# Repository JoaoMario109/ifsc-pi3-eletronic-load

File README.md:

<div id="top"></div>

<!-- PROJECT LOGO -->
<br />
<div align="center">

  <h3 align="center">Simple Electronic Load</h3>

  <p align="center">
    <br />
    <br />
    <a href="https://github.com/JoaoMario109/ifsc-pi3-eletronic-load/issues">Report Bug</a>
    ·
    <a href="https://github.com/JoaoMario109/ifsc-pi3-eletronic-load/issues">Request Feature</a>
  </p>
</div>

<!-- TABLE OF CONTENTS -->
<details>
  <summary>Table of Contents</summary>
  <ol>
    <li>
      <a href="#about-the-project">About The Project</a>
      <ul>
        <li><a href="#about-the-project-overview">Overview</a></li>
      </ul>
    </li>
    <li>
      <a href="#license">License</a>
    </li>
    <li>
      <a href="#contact">Contacts</a>
    </li>
  </ol>
</details>

<!-- ABOUT THE PROJECT -->
<div id="about-the-project"></div>

## About The Project

This project is the implementation of a simple electronic load with WiFi integration and the ability to operate using custom waveforms. It forms part of (PI3) for the Electronics Engineering course at IFSC, Campus Florianópolis.

<div id="about-the-project-overview"></div>

### Overview

The electronic load is designed to handle up to 100W of power and supports four different operating modes: constant current, constant power, constant resistance, and constant voltage. Additionally, it can execute custom waveforms uploaded via its various communication interfaces.

The load is divided into three key modules:
1. **Power Module** – Contains the hardware components responsible for handling the load, such as the power transistors and other essential elements.
2. **Control Module** – Manages the desired operating mode and ensures the system maintains the appropriate levels of current, voltage, or resistance.
3. **Communication Module** – Facilitates interaction between the user and the device via WiFi, USB, or other interfaces, and stores custom waveforms on an SD card for future use.

The device can be accessed through its control panel, WiFi, or USB interface, and its communication capabilities can easily be expanded. Any compatible interface can be connected to the main I2C bus using an SCPI-like protocol.

<p align="right">(<a href="#top">back to top</a>)</p>

<!-- LICENSE -->
<div id="license"></div>

## License

Distributed under the MIT License. See [LICENSE](LICENSE) for more information.

<p align="right">(<a href="#top">back to top</a>)</p>

<hr />

<!-- CONTACT -->
<div id="contact"></div>

## Contact

Alejo Perdomo Milar [alejo.pm@aluno.ifsc.edu.br](alejo.pm@aluno.ifsc.edu.br)\
João Mário Carnieletto Izoton Lago [joao.mcil2003@aluno.ifsc.edu.br](joao.mcil2003@aluno.ifsc.edu.br)\
Paulo Cezar Ventura Junior [paulo.cvj@aluno.ifsc.edu.br](paulo.cvj@aluno.ifsc.edu.br)

Project Link: [https://github.com/JoaoMario109/ifsc-pi3-eletronic-load](https://github.com/JoaoMario109/ifsc-pi3-eletronic-load)

<p align="right">(<a href="#top">back to top</a>)</p>

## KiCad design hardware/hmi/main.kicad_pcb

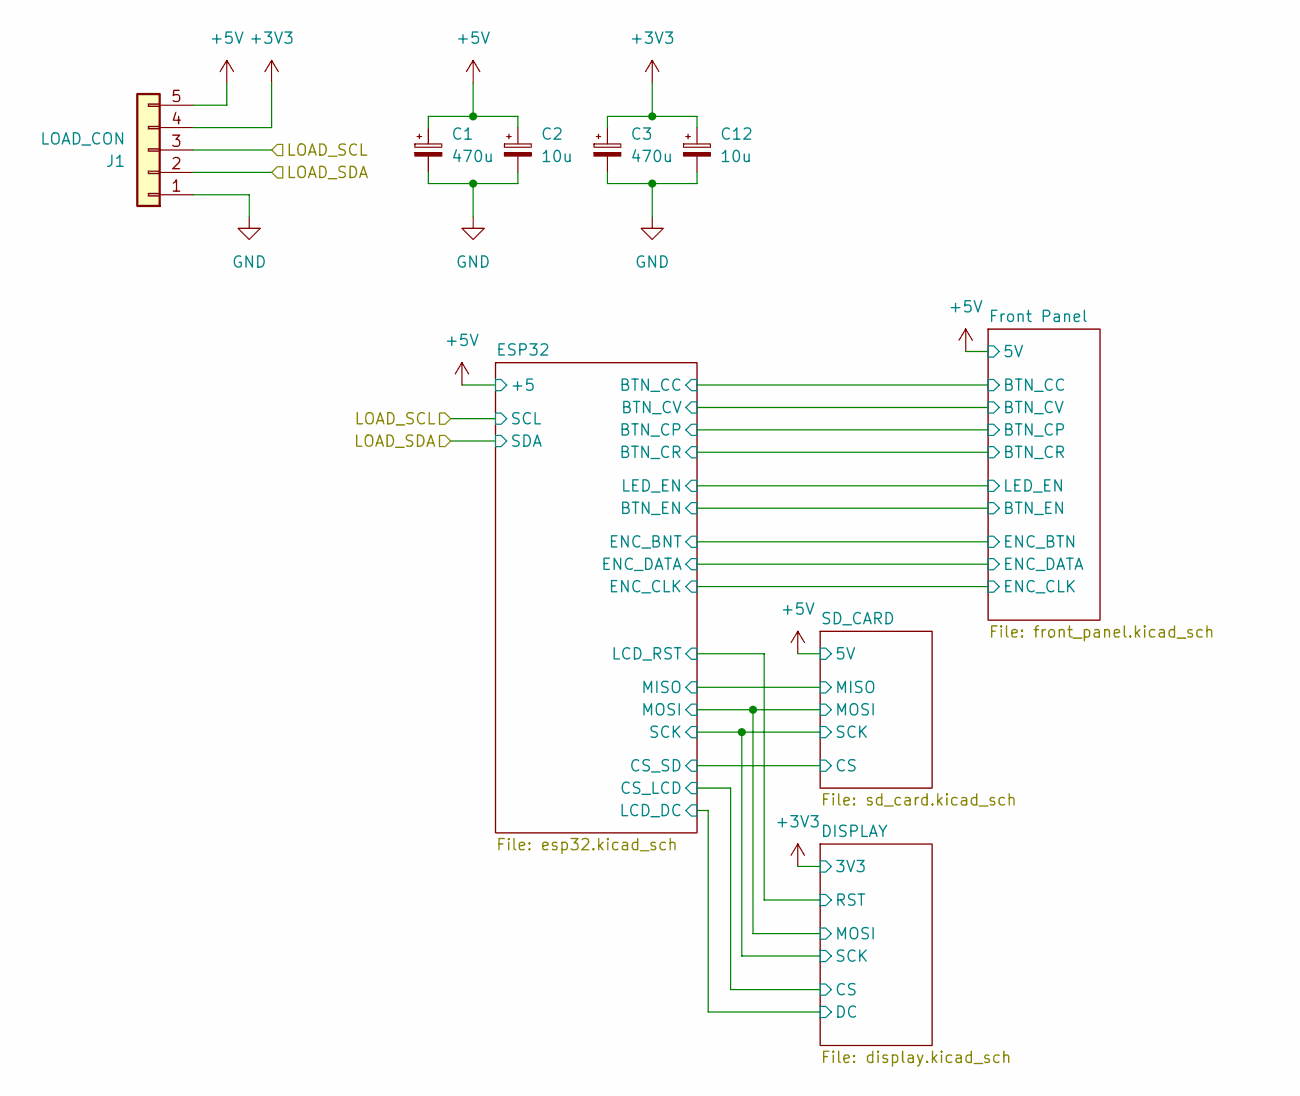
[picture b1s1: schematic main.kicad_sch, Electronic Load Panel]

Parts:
C1, C3: 470u; CP_Radial_D8.0mm_P5.00mm
C2, C12: 10u; CP_Radial_D5.0mm_P2.50mm
J1: LOAD_CON; PinSocket_1x05_P2.54mm_Vertical

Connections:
+3V3: C3.1, C12.1, J1.4; also elsewhere on the board
+5V: C1.1, C2.1, J1.5; also elsewhere on the board
/LOAD_SCL: J1.3; also elsewhere on the board
/LOAD_SDA: J1.2; also elsewhere on the board
GND: C1.2, C2.2, C3.2, C12.2, J1.1; also elsewhere on the board

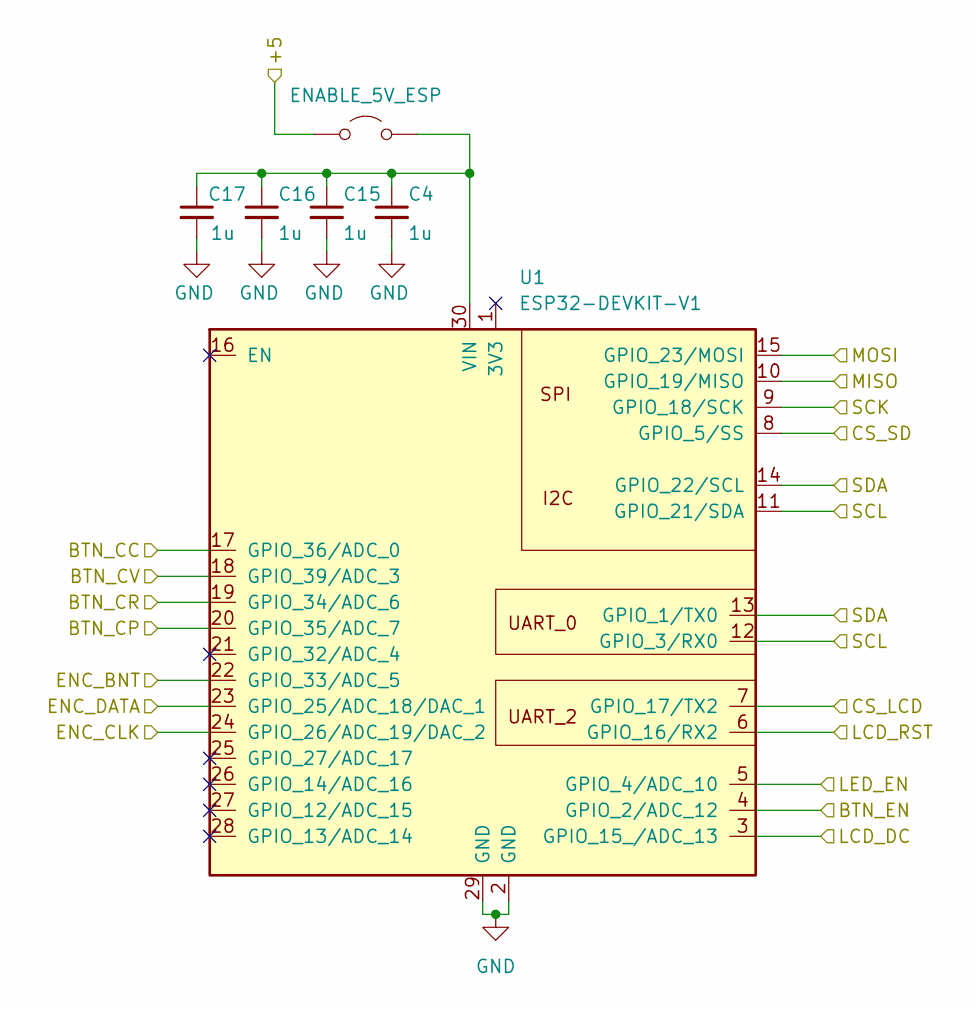
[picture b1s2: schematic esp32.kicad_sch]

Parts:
C4, C15, C16, C17: 1u; C_0805_2012Metric_Pad1.18x1.45mm_HandSolder
JP1: ENABLE_5V_ESP; SolderJumper-2_P1.3mm_Open_TrianglePad1.0x1.5mm
U1: ESP32-DEVKIT-V1; ESP32--DEVKIT-V1

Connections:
+5V: JP1.1 (A); also elsewhere on the board
/DISPLAY/CS: U1.7 (GPIO_17/TX2); also elsewhere on the board
/DISPLAY/DC: U1.3 (GPIO_15_/ADC_13); also elsewhere on the board
/DISPLAY/MOSI: U1.15 (GPIO_23/MOSI); also elsewhere on the board
/DISPLAY/RST: U1.6 (GPIO_16/RX2); also elsewhere on the board
/DISPLAY/SCK: U1.9 (GPIO_18/SCK); also elsewhere on the board
/ESP32/BTN_CC: U1.17 (GPIO_36/ADC_0); also elsewhere on the board
/ESP32/BTN_CP: U1.20 (GPIO_35/ADC_7); also elsewhere on the board
/ESP32/BTN_CR: U1.19 (GPIO_34/ADC_6); also elsewhere on the board
/ESP32/BTN_CV: U1.18 (GPIO_39/ADC_3); also elsewhere on the board
/ESP32/BTN_EN: U1.4 (GPIO_2/ADC_12); also elsewhere on the board
/ESP32/CS_SD: U1.8 (GPIO_5/SS); also elsewhere on the board
/ESP32/ENC_BNT: U1.22 (GPIO_33/ADC_5); also elsewhere on the board
/ESP32/ENC_CLK: U1.24 (GPIO_26/ADC_19/DAC_2); also elsewhere on the board
/ESP32/ENC_DATA: U1.23 (GPIO_25/ADC_18/DAC_1); also elsewhere on the board
/ESP32/LED_EN: U1.5 (GPIO_4/ADC_10); also elsewhere on the board
/ESP32/MISO: U1.10 (GPIO_19/MISO); also elsewhere on the board
/LOAD_SCL: U1.11 (GPIO_21/SDA), U1.12 (GPIO_3/RX0); also elsewhere on the board
/LOAD_SDA: U1.13 (GPIO_1/TX0), U1.14 (GPIO_22/SCL); also elsewhere on the board
GND: C4.2, C15.2, C16.2, C17.2, U1.2 (GND), U1.29 (GND); also elsewhere on the board
unnamed: C4.1, C15.1, C16.1, C17.1, JP1.2 (B), U1.30 (VIN)

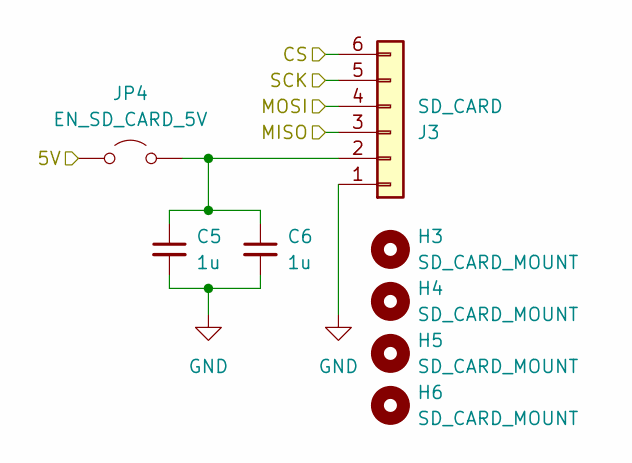
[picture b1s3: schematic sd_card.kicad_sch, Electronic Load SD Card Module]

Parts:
C5, C6: 1u; C_0805_2012Metric_Pad1.18x1.45mm_HandSolder
H3, H4, H5, H6: SD_CARD_MOUNT; MountingHole_2.2mm_M2
J3: SD_CARD; PinSocket_1x06_P2.54mm_Vertical
JP4: EN_SD_CARD_5V; SolderJumper-2_P1.3mm_Open_TrianglePad1.0x1.5mm

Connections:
+5V: JP4.1 (A); also elsewhere on the board
/DISPLAY/MOSI: J3.4; also elsewhere on the board
/DISPLAY/SCK: J3.5; also elsewhere on the board
/ESP32/CS_SD: J3.6; also elsewhere on the board
/ESP32/MISO: J3.3; also elsewhere on the board
GND: C5.2, C6.2, J3.1; also elsewhere on the board
unnamed: C5.1, C6.1, J3.2, JP4.2 (B)

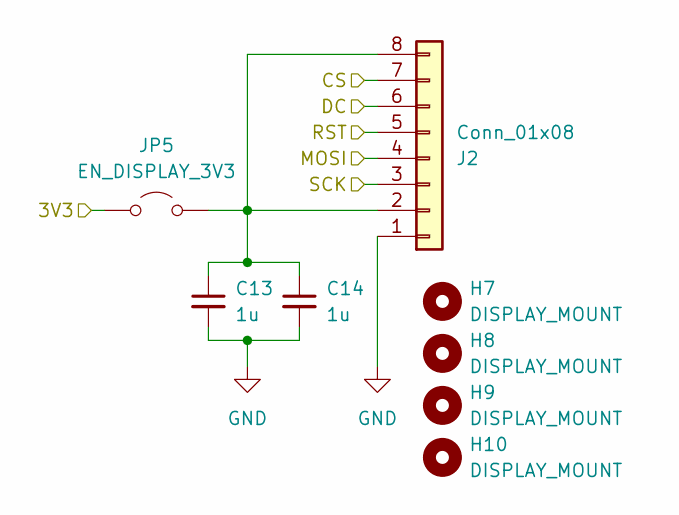
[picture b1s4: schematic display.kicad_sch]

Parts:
C13, C14: 1u; C_0805_2012Metric_Pad1.18x1.45mm_HandSolder
H7, H8, H9, H10: DISPLAY_MOUNT; MountingHole_2.2mm_M2
J2: Conn_01x08; PinSocket_1x08_P2.54mm_Vertical
JP5: EN_DISPLAY_3V3; SolderJumper-2_P1.3mm_Open_TrianglePad1.0x1.5mm

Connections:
+3V3: JP5.1 (A); also elsewhere on the board
/DISPLAY/CS: J2.7; also elsewhere on the board
/DISPLAY/DC: J2.6; also elsewhere on the board
/DISPLAY/MOSI: J2.4; also elsewhere on the board
/DISPLAY/RST: J2.5; also elsewhere on the board
/DISPLAY/SCK: J2.3; also elsewhere on the board
GND: C13.2, C14.2, J2.1; also elsewhere on the board
unnamed: C13.1, C14.1, J2.2, J2.8, JP5.2 (B)

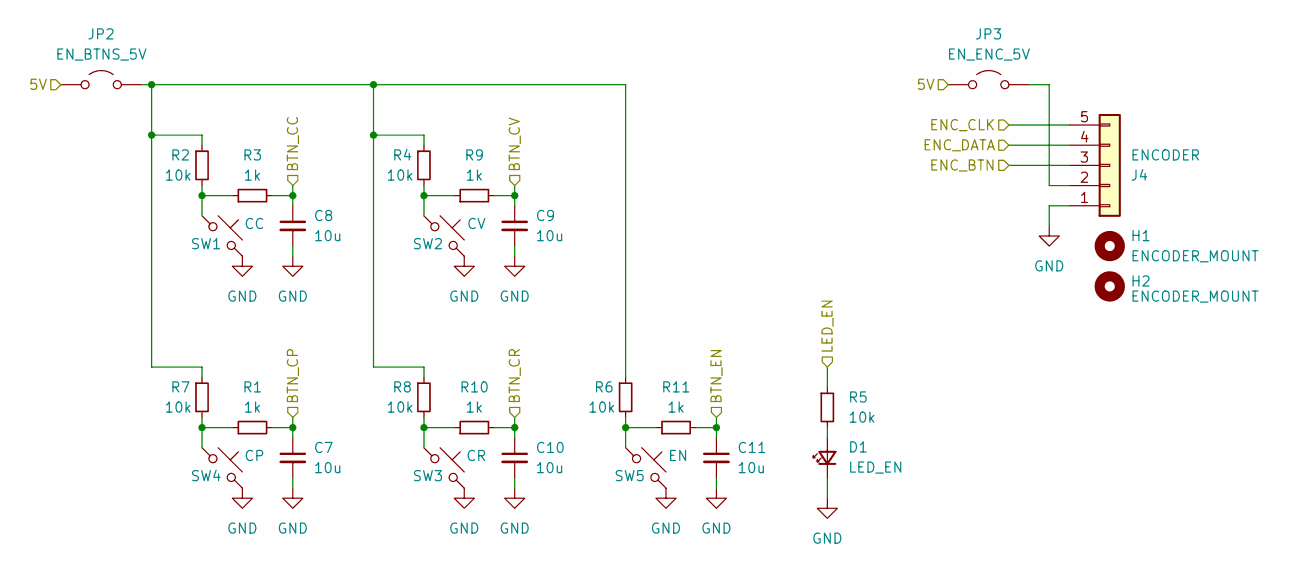
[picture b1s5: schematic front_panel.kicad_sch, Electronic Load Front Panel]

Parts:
C7, C8, C9, C10, C11: 10u; C_0805_2012Metric_Pad1.18x1.45mm_HandSolder
D1: LED_EN; LED_D3.0mm
H1, H2: ENCODER_MOUNT; MountingHole_3mm
J4: ENCODER; PinSocket_1x05_P2.54mm_Vertical
JP2: EN_BTNS_5V; SolderJumper-2_P1.3mm_Open_TrianglePad1.0x1.5mm
JP3: EN_ENC_5V; SolderJumper-2_P1.3mm_Open_TrianglePad1.0x1.5mm
R1, R3, R9, R10, R11: 1k; R_0805_2012Metric_Pad1.20x1.40mm_HandSolder
R2, R4, R5, R6, R7, R8: 10k; R_0805_2012Metric_Pad1.20x1.40mm_HandSolder
SW1: CC; SW_PUSH-12mm_Wuerth-430476085716
SW2: CV; SW_PUSH-12mm_Wuerth-430476085716
SW3: CR; SW_PUSH-12mm_Wuerth-430476085716
SW4: CP; SW_PUSH-12mm_Wuerth-430476085716
SW5: EN; SW_PUSH-12mm_Wuerth-430476085716

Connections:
+5V: JP2.1 (A), JP3.1 (A); also elsewhere on the board
/ESP32/BTN_CC: C8.1, R3.2; also elsewhere on the board
/ESP32/BTN_CP: C7.1, R1.2; also elsewhere on the board
/ESP32/BTN_CR: C10.1, R10.2; also elsewhere on the board
/ESP32/BTN_CV: C9.1, R9.2; also elsewhere on the board
/ESP32/BTN_EN: C11.1, R11.2; also elsewhere on the board
/ESP32/ENC_BNT: J4.3; also elsewhere on the board
/ESP32/ENC_CLK: J4.5; also elsewhere on the board
/ESP32/ENC_DATA: J4.4; also elsewhere on the board
/ESP32/LED_EN: R5.1; also elsewhere on the board
GND: C7.2, C8.2, C9.2, C10.2, C11.2, D1.1 (K), J4.1, SW1.2, SW2.2, SW3.2, SW4.2, SW5.2; also elsewhere on the board
unnamed: D1.2 (A), R5.2
unnamed: J4.2, JP3.2 (B)
unnamed: JP2.2 (B), R2.1, R4.1, R6.1, R7.1, R8.1
unnamed: R1.1, R7.2, SW4.1
unnamed: R2.2, R3.1, SW1.1
unnamed: R4.2, R9.1, SW2.1
unnamed: R8.2, R10.1, SW3.1
unnamed: R6.2, R11.1, SW5.1

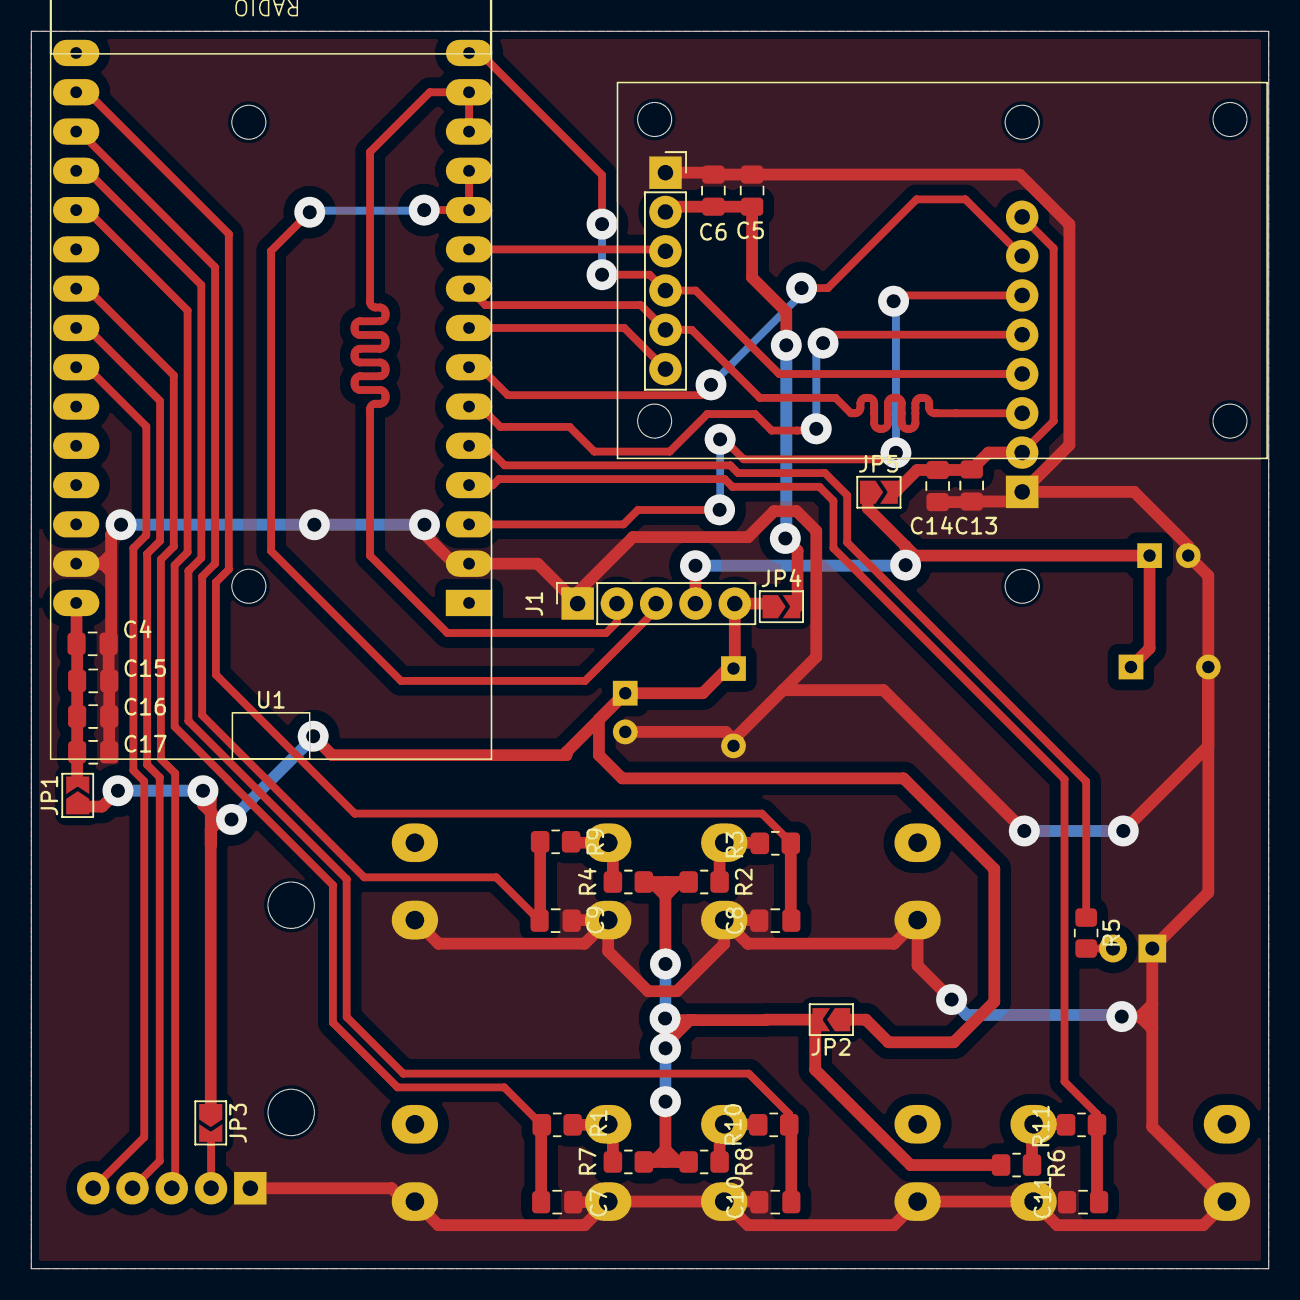
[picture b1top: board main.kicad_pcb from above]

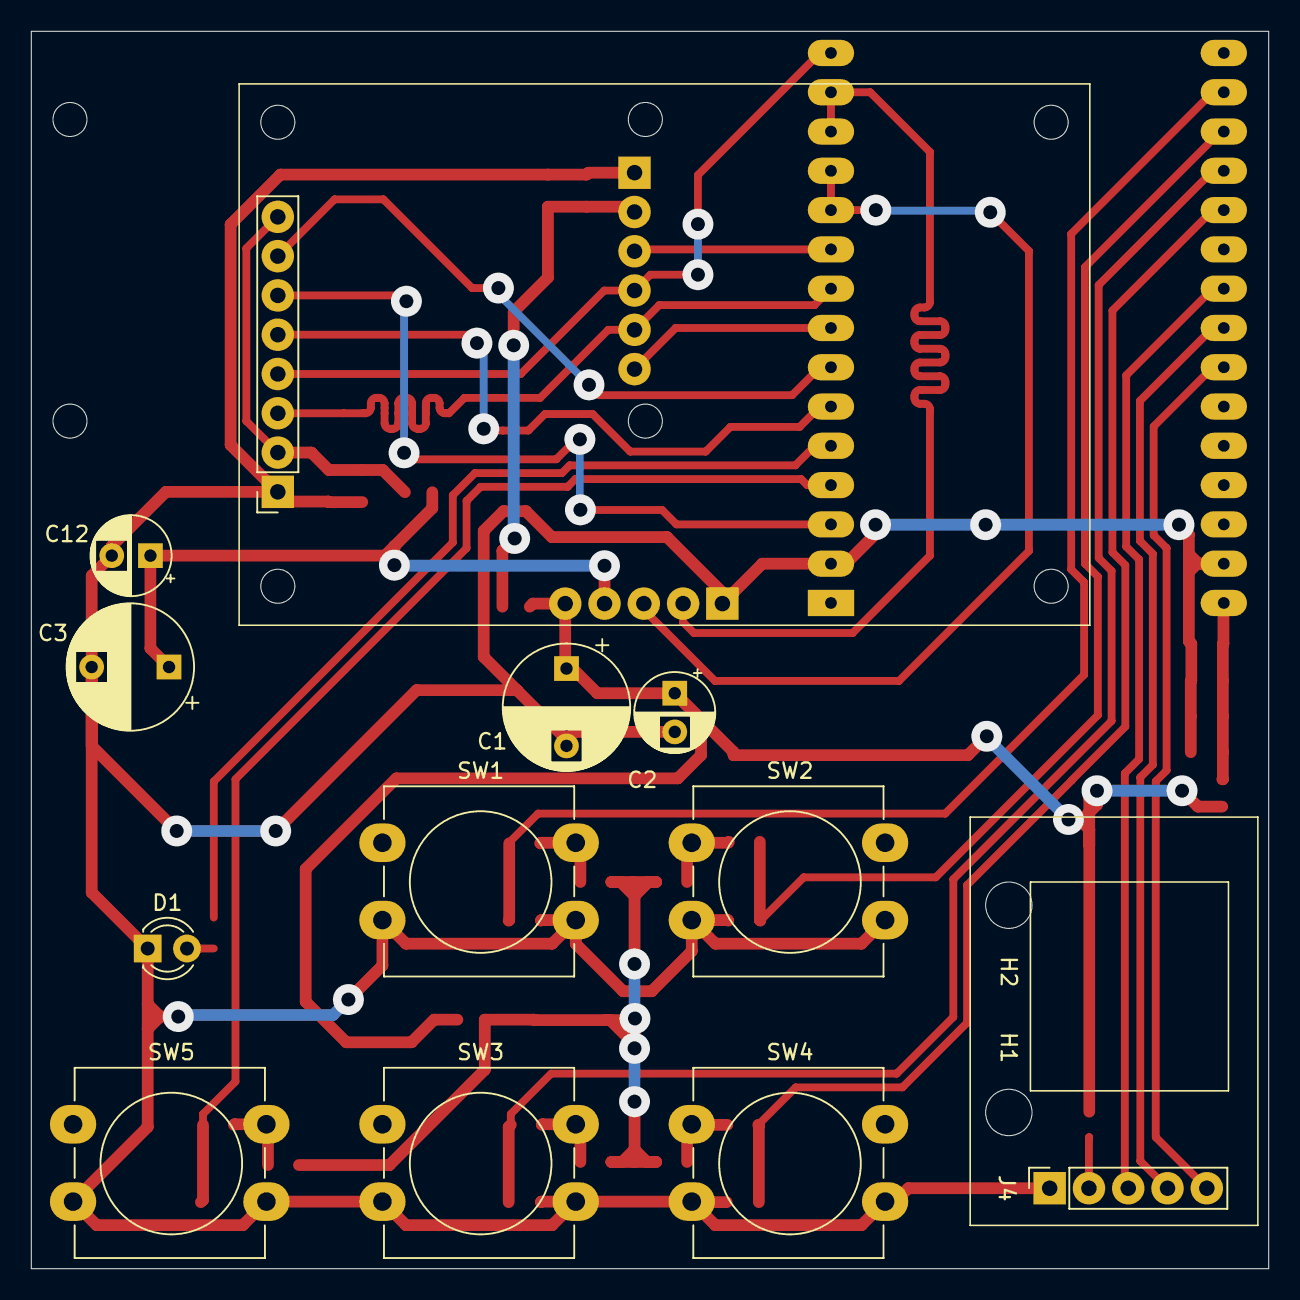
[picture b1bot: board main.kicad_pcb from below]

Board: 2 copper layers, 80.0 x 80.0 mm, 54 parts (18 on the bottom side), 32 nets.

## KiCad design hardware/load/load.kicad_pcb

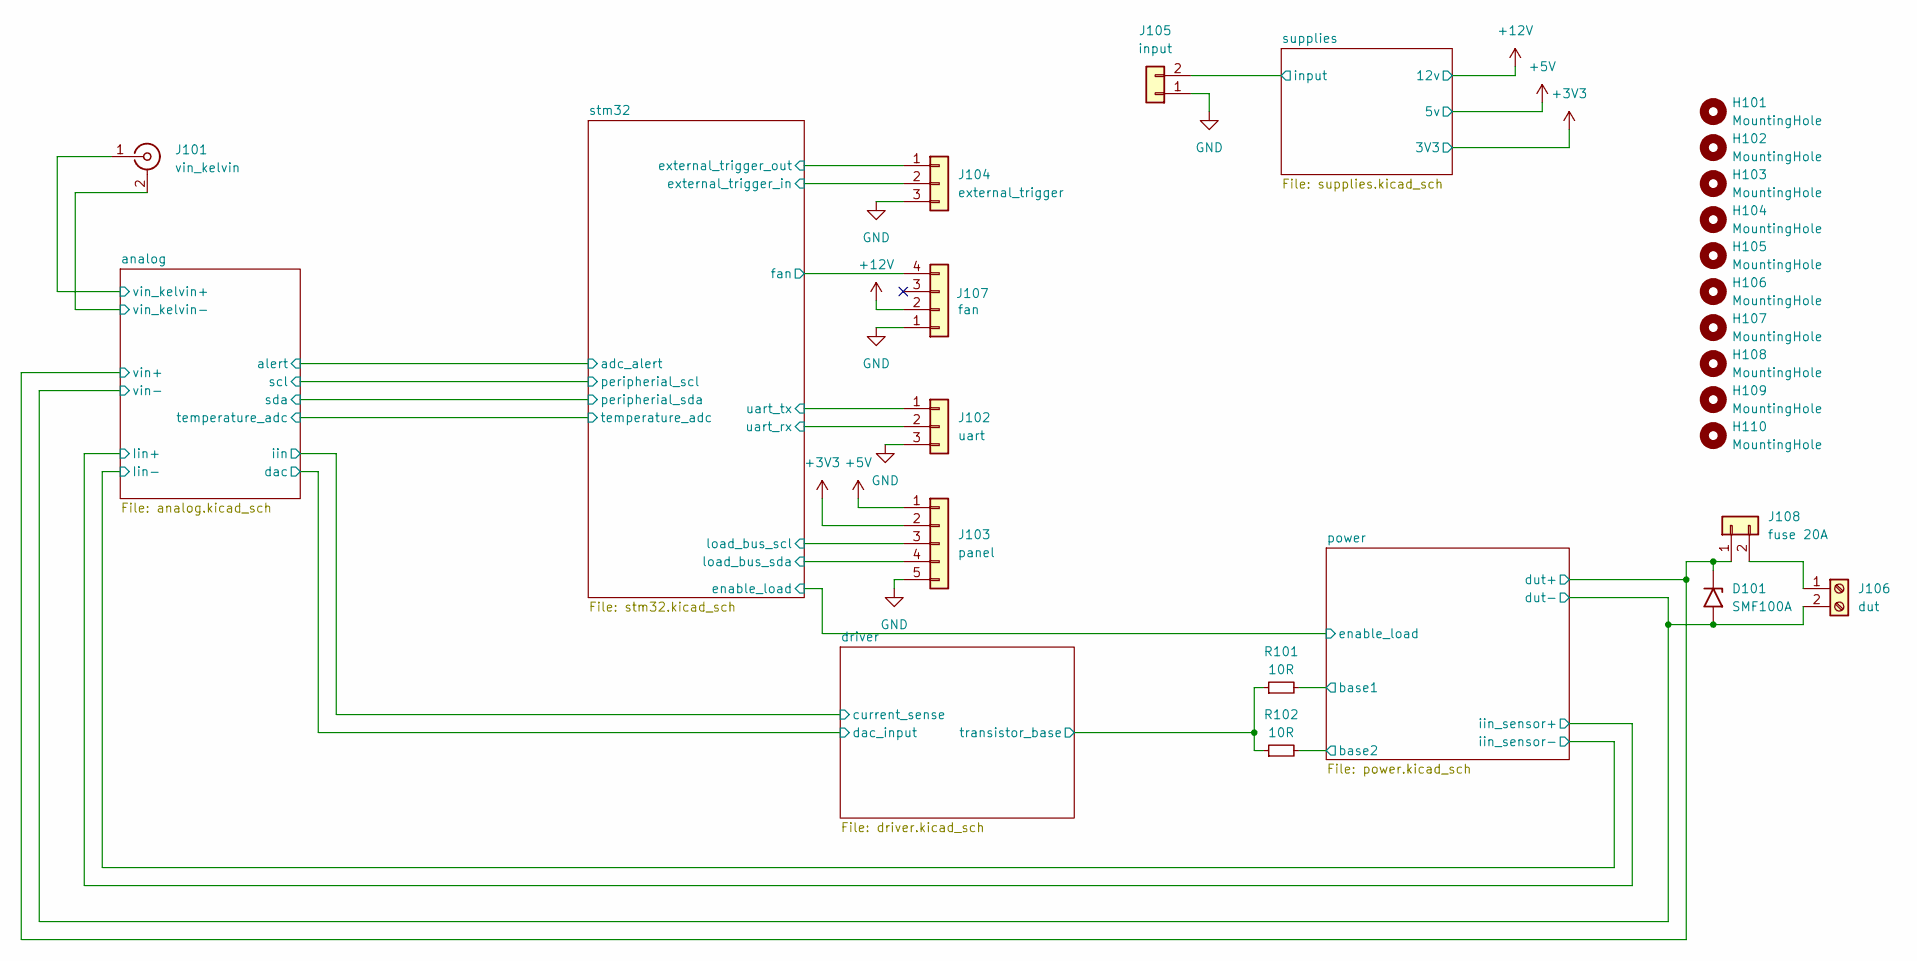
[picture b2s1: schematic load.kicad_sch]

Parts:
D101: SMF100A; D_SMF
H101, H102, H103, H104, H105, H106, H107, H108, H109, H110: MountingHole; MountingHole_3.2mm_M3
J101: vin_kelvin; RCA
J102: uart; PinHeader_1x03_P2.54mm_Vertical
J103: panel; PinHeader_1x05_P2.54mm_Vertical
J104: external_trigger; TerminalBlock_bornier-3_P5.08mm
J105: input; TerminalBlock_bornier-2_P5.08mm
J106: dut; Banana_PCB_2Pin
J107: fan; FanPinHeader_1x04_P2.54mm_Vertical
J108: fuse 20A; TerminalBlock_bornier-2_P5.08mm
R101, R102: 10R; R_0805_2012Metric_Pad1.20x1.40mm_HandSolder

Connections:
+3V3: J103.2; also elsewhere on the board
+5V: J103.1; also elsewhere on the board
+12V: J107.2; also elsewhere on the board
/analog/vin+: D101.1 (A1), J108.1; also elsewhere on the board
/analog/vin_kelvin+: J101.1 (In); also elsewhere on the board
/analog/vin_kelvin-: J101.2 (Ext); also elsewhere on the board
/driver/transistor_base: R101.1, R102.1; also elsewhere on the board
/power/base1: R101.2; also elsewhere on the board
/power/base2: R102.2; also elsewhere on the board
/stm32/external_trigger_in: J104.2; also elsewhere on the board
/stm32/external_trigger_out: J104.1; also elsewhere on the board
/stm32/fan: J107.4; also elsewhere on the board
/stm32/load_bus_scl: J103.3; also elsewhere on the board
/stm32/load_bus_sda: J103.4; also elsewhere on the board
/stm32/uart_rx: J102.2; also elsewhere on the board
/stm32/uart_tx: J102.1; also elsewhere on the board
/supplies/input: J105.2; also elsewhere on the board
GND: J102.3, J103.5, J104.3, J105.1, J107.1; also elsewhere on the board
GNDPWR: D101.2 (A2), J106.2; also elsewhere on the board
unnamed: J106.1, J108.2

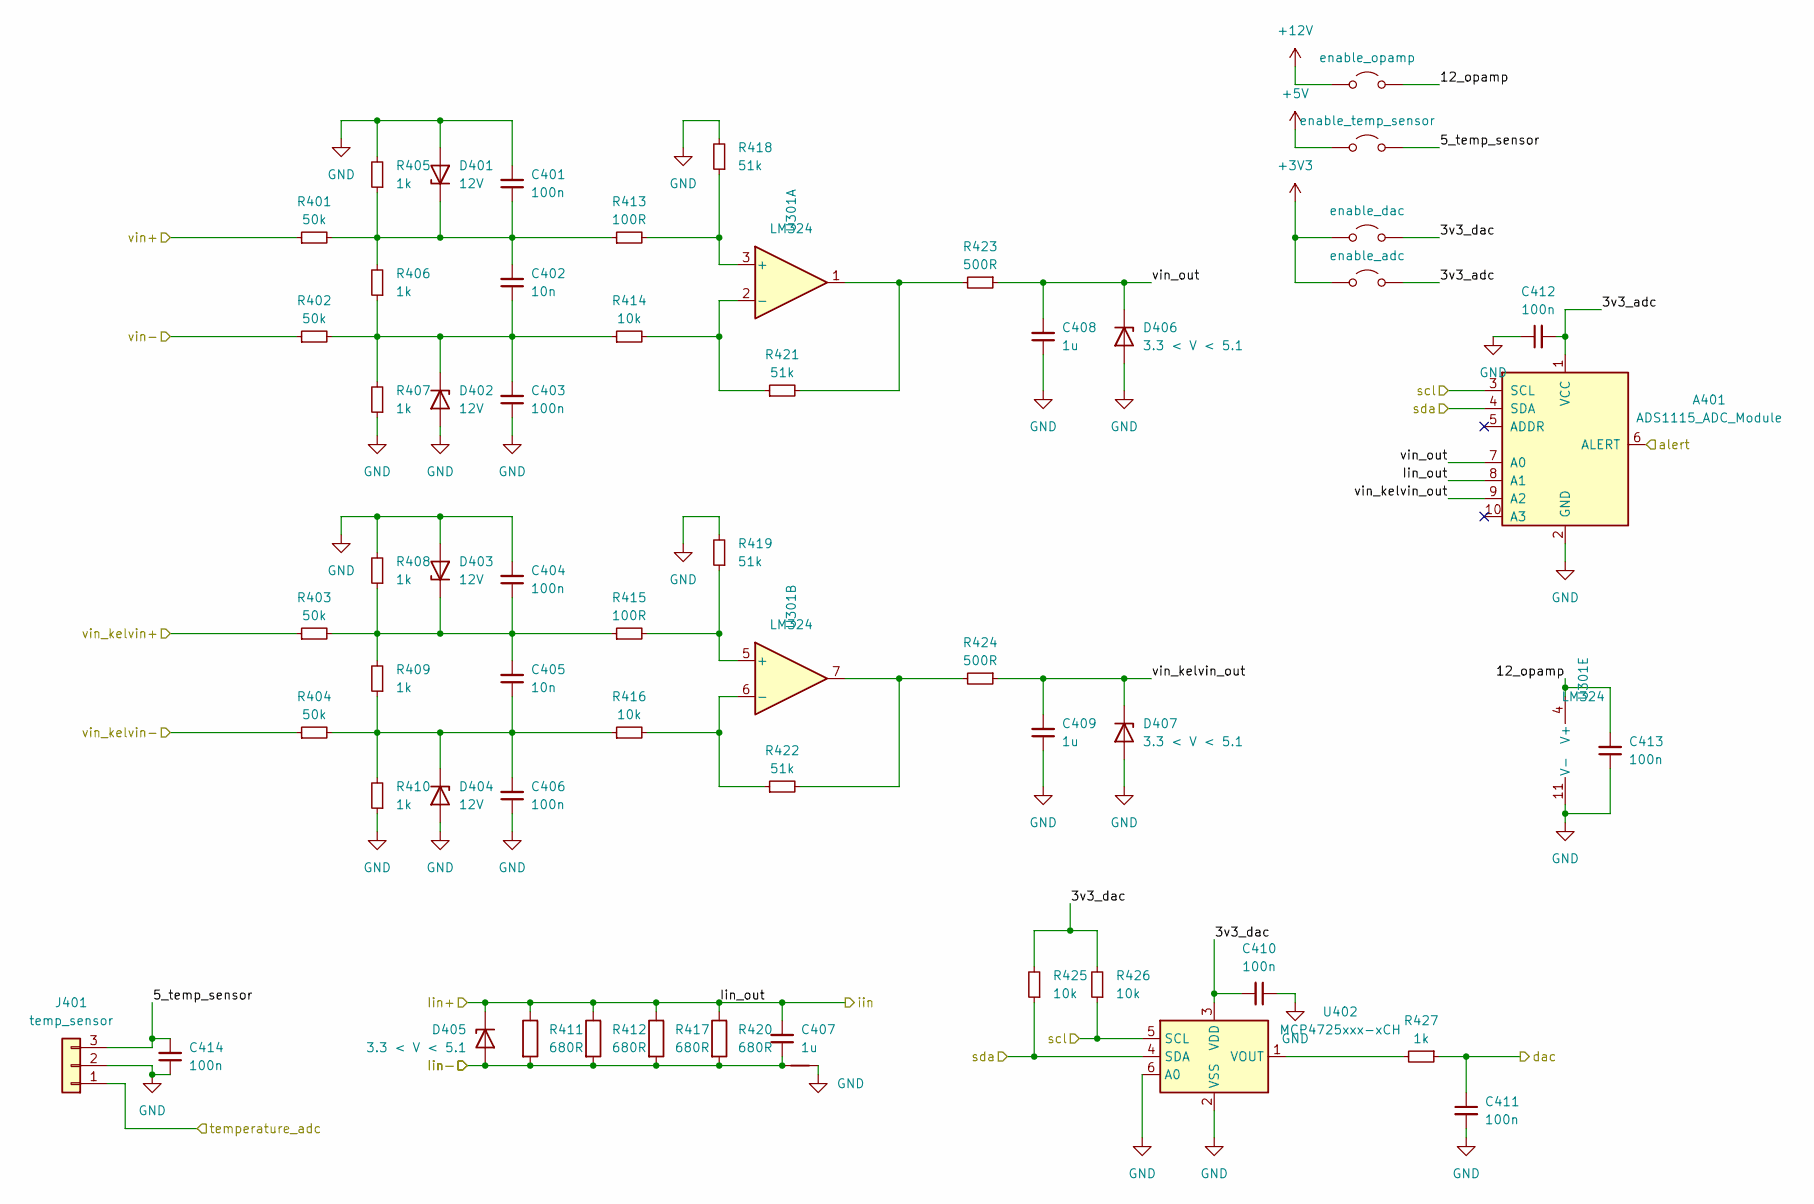
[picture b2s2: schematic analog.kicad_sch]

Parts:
A401: ADS1115_ADC_Module; ADC1115_ADC_Module
C401, C403, C404, C406, C410, C411, C412, C413, C414: 100n; C_0805_2012Metric_Pad1.18x1.45mm_HandSolder
C402, C405: 10n; C_0805_2012Metric_Pad1.18x1.45mm_HandSolder
C407, C408, C409: 1u; C_0805_2012Metric_Pad1.18x1.45mm_HandSolder
D401, D402, D403, D404: 12V; D_MiniMELF
D405, D406, D407: 3.3 < V < 5.1; D_MiniMELF
J401: temp_sensor; PinHeader_1x03_P2.54mm_Vertical
JP401: enable_dac; SolderJumper-2_P1.3mm_Open_TrianglePad1.0x1.5mm
JP402: enable_adc; SolderJumper-2_P1.3mm_Open_TrianglePad1.0x1.5mm
JP403: enable_opamp; SolderJumper-2_P1.3mm_Open_TrianglePad1.0x1.5mm
JP404: enable_temp_sensor; SolderJumper-2_P1.3mm_Open_TrianglePad1.0x1.5mm
NT401: NetTie_2; NetTie-2_SMD_Pad0.5mm
R401, R402, R403, R404: 50k; R_0805_2012Metric_Pad1.20x1.40mm_HandSolder
R405, R406, R407, R408, R409, R410, R427: 1k; R_0805_2012Metric_Pad1.20x1.40mm_HandSolder
R411, R412, R417, R420: 680R; R_0805_2012Metric_Pad1.20x1.40mm_HandSolder
R413, R415: 100R; R_0805_2012Metric_Pad1.20x1.40mm_HandSolder
R414, R416, R425, R426: 10k; R_0805_2012Metric_Pad1.20x1.40mm_HandSolder
R418, R419, R421, R422: 51k; R_0805_2012Metric_Pad1.20x1.40mm_HandSolder
R423, R424: 500R; R_0805_2012Metric_Pad1.20x1.40mm_HandSolder
U301: LM324; SOIC-14_3.9x8.7mm_P1.27mm
U402: MCP4725xxx-xCH; SOT-23-6

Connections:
+3V3: JP401.1 (A), JP402.2 (B); also elsewhere on the board
+5V: JP404.2 (B); also elsewhere on the board
+12V: JP403.2 (B); also elsewhere on the board
/analog/3v3_adc: A401.1 (VCC), C412.2, JP402.1 (A)
/analog/3v3_dac: C410.2, JP401.2 (B), R425.2, R426.2, U402.3 (VDD)
/analog/5_temp_sensor: C414.2, J401.3, JP404.1 (A)
/analog/12_opamp: C413.2, JP403.1 (A), U301.4 (V+)
/analog/Iin-: C407.1, D405.2 (A), NT401.2, R411.2, R412.2, R417.2, R420.2; also elsewhere on the board
/analog/Iin_out: A401.8 (A1), C407.2, D405.1 (K), R411.1, R412.1, R417.1, R420.1; also elsewhere on the board
/analog/alert: A401.6 (ALERT); also elsewhere on the board
/analog/dac: C411.1, R427.1; also elsewhere on the board
/analog/scl: A401.3 (SCL), R426.1, U402.5 (SCL); also elsewhere on the board
/analog/sda: A401.4 (SDA), R425.1, U402.4 (SDA); also elsewhere on the board
/analog/temperature_adc: J401.1; also elsewhere on the board
/analog/vin+: R401.1; also elsewhere on the board
/analog/vin_kelvin+: R403.1; also elsewhere on the board
/analog/vin_kelvin-: R404.1; also elsewhere on the board
/analog/vin_kelvin_out: A401.9 (A2), C409.2, D407.1 (K), R424.1
/analog/vin_out: A401.7 (A0), C408.2, D406.1 (K), R423.1
GND: A401.2 (GND), C401.2, C403.1, C404.2, C406.1, C408.1, C409.1, C410.1, C411.2, C412.1, C413.1, C414.1, D401.2 (A), D402.2 (A), D403.2 (A), D404.2 (A), D406.2 (A), D407.2 (A), J401.2, NT401.1, R405.2, R407.1, R408.2, R410.1, R418.2, R419.2, U301.11 (V-), U402.2 (VSS), U402.6 (A0); also elsewhere on the board
GNDPWR: R402.1; also elsewhere on the board
unnamed: C401.1, C402.2, D401.1 (K), R401.2, R405.1, R406.2, R413.1
unnamed: C402.1, C403.2, D402.1 (K), R402.2, R406.1, R407.2, R414.1
unnamed: C404.1, C405.2, D403.1 (K), R403.2, R408.1, R409.2, R415.1
unnamed: C405.1, C406.2, D404.1 (K), R404.2, R409.1, R410.2, R416.1
unnamed: R421.2, R423.2, U301.1
unnamed: R422.2, R424.2, U301.7
unnamed: R413.2, R418.1, U301.3 (+)
unnamed: R414.2, R421.1, U301.2 (-)
unnamed: R415.2, R419.1, U301.5 (+)
unnamed: R416.2, R422.1, U301.6 (-)
unnamed: R427.2, U402.1 (VOUT)

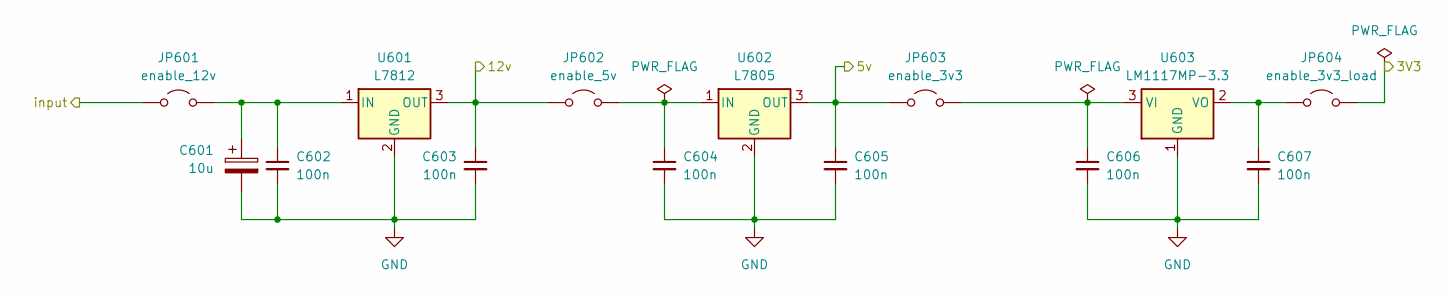
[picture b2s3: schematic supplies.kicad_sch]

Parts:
C601: 10u; CP_Radial_D8.0mm_P3.50mm
C602, C603, C604, C605, C606, C607: 100n; C_0805_2012Metric_Pad1.18x1.45mm_HandSolder
JP601: enable_12v; SolderJumper-2_P1.3mm_Open_TrianglePad1.0x1.5mm
JP602: enable_5v; SolderJumper-2_P1.3mm_Open_TrianglePad1.0x1.5mm
JP603: enable_3v3; SolderJumper-2_P1.3mm_Open_TrianglePad1.0x1.5mm
JP604: enable_3v3_load; SolderJumper-2_P1.3mm_Open_TrianglePad1.0x1.5mm
U601: L7812; TO-220-3_Vertical
U602: L7805; TO-220-3_Vertical
U603: LM1117MP-3.3; SOT-223-3_TabPin2

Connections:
+3V3: JP604.2 (B); also elsewhere on the board
+5V: C605.1, JP603.1 (A), U602.3 (OUT); also elsewhere on the board
+12V: C603.1, JP602.1 (A), U601.3 (OUT); also elsewhere on the board
/supplies/input: JP601.1 (A); also elsewhere on the board
GND: C601.2, C602.2, C603.2, C604.2, C605.2, C606.2, C607.2, U601.2 (GND), U602.2 (GND), U603.1 (GND); also elsewhere on the board
unnamed: C601.1, C602.1, JP601.2 (B), U601.1 (IN)
unnamed: C604.1, JP602.2 (B), U602.1 (IN)
unnamed: C606.1, JP603.2 (B), U603.3 (VI)
unnamed: C607.1, JP604.1 (A), U603.2 (VO)

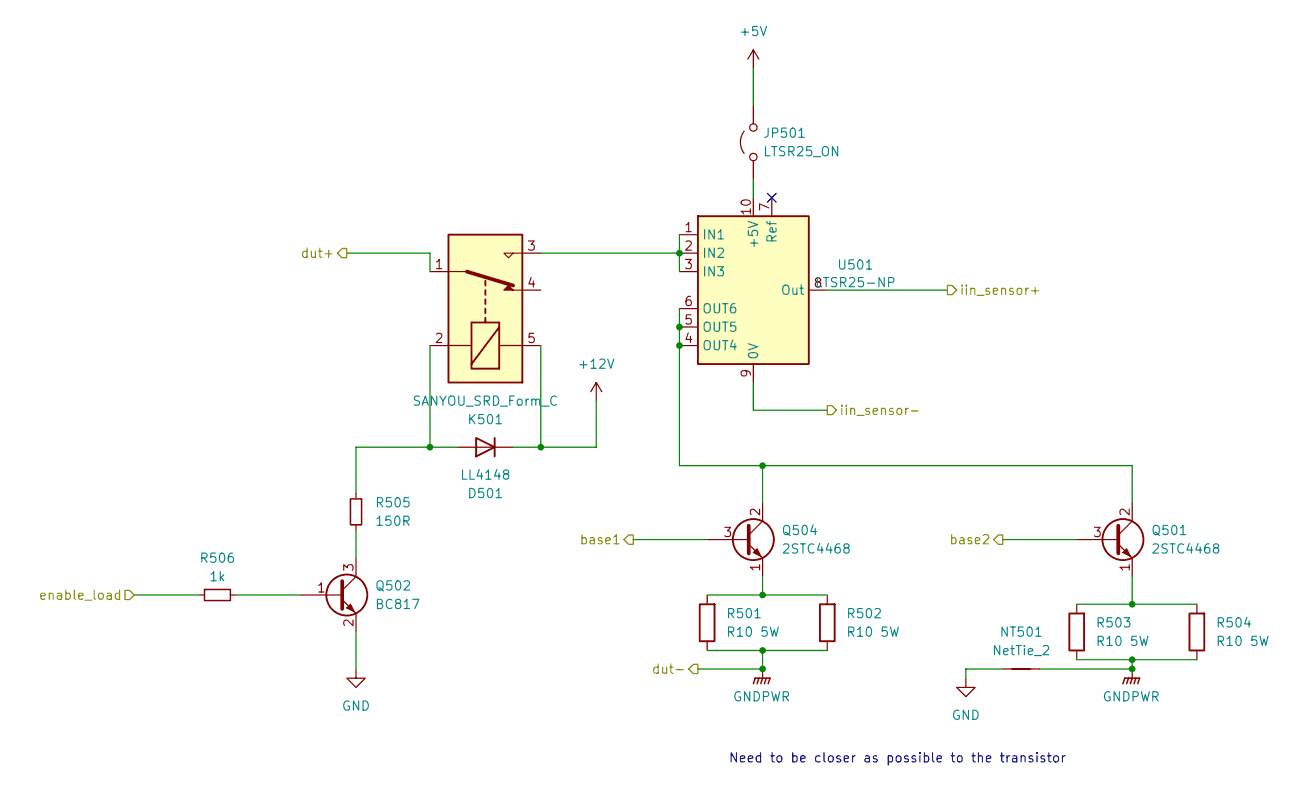
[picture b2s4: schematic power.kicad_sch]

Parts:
D501: LL4148; D_MiniMELF
JP501: LTSR25_ON; SolderJumper-2_P1.3mm_Open_TrianglePad1.0x1.5mm
K501: SANYOU_SRD_Form_C; Relay_SPDT_SANYOU_SRD_Series_Form_C
NT501: NetTie_2; NetTie-2_SMD_Pad0.5mm
Q501, Q504: 2STC4468; TerminalBlock_bornier-3_P5.08mm
Q502: BC817; SOT-23
R501, R502, R503, R504: R10 5W; R_Box_L14.0mm_W5.0mm_P9.00mm
R505: 150R; R_0805_2012Metric_Pad1.20x1.40mm_HandSolder
R506: 1k; R_0805_2012Metric_Pad1.20x1.40mm_HandSolder
U501: LTSR25-NP; LEM_LTSR-NP

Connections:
+5V: JP501.2 (B); also elsewhere on the board
+12V: D501.1 (K), K501.5; also elsewhere on the board
/analog/Iin-: U501.9 (0V); also elsewhere on the board
/analog/Iin_out: U501.8 (Out); also elsewhere on the board
/analog/vin+: K501.1; also elsewhere on the board
/power/base1: Q504.3 (B); also elsewhere on the board
/power/base2: Q501.3 (B); also elsewhere on the board
/power/enable_load: R506.1
GND: NT501.2, Q502.2 (E); also elsewhere on the board
GNDPWR: NT501.1, R501.1, R502.1, R503.1, R504.1; also elsewhere on the board
unnamed: D501.2 (A), K501.2, R505.1
unnamed: JP501.1 (A), U501.10 (+5V)
unnamed: Q501.2 (C), Q504.2 (C), U501.4 (OUT4), U501.5 (OUT5), U501.6 (OUT6)
unnamed: Q501.1 (E), R503.2, R504.2
unnamed: Q502.1 (B), R506.2
unnamed: Q502.3 (C), R505.2
unnamed: Q504.1 (E), R501.2, R502.2
unnamed: K501.3, U501.1 (IN1), U501.2 (IN2), U501.3 (IN3)

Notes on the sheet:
Need to be closer as possible to the transistor
